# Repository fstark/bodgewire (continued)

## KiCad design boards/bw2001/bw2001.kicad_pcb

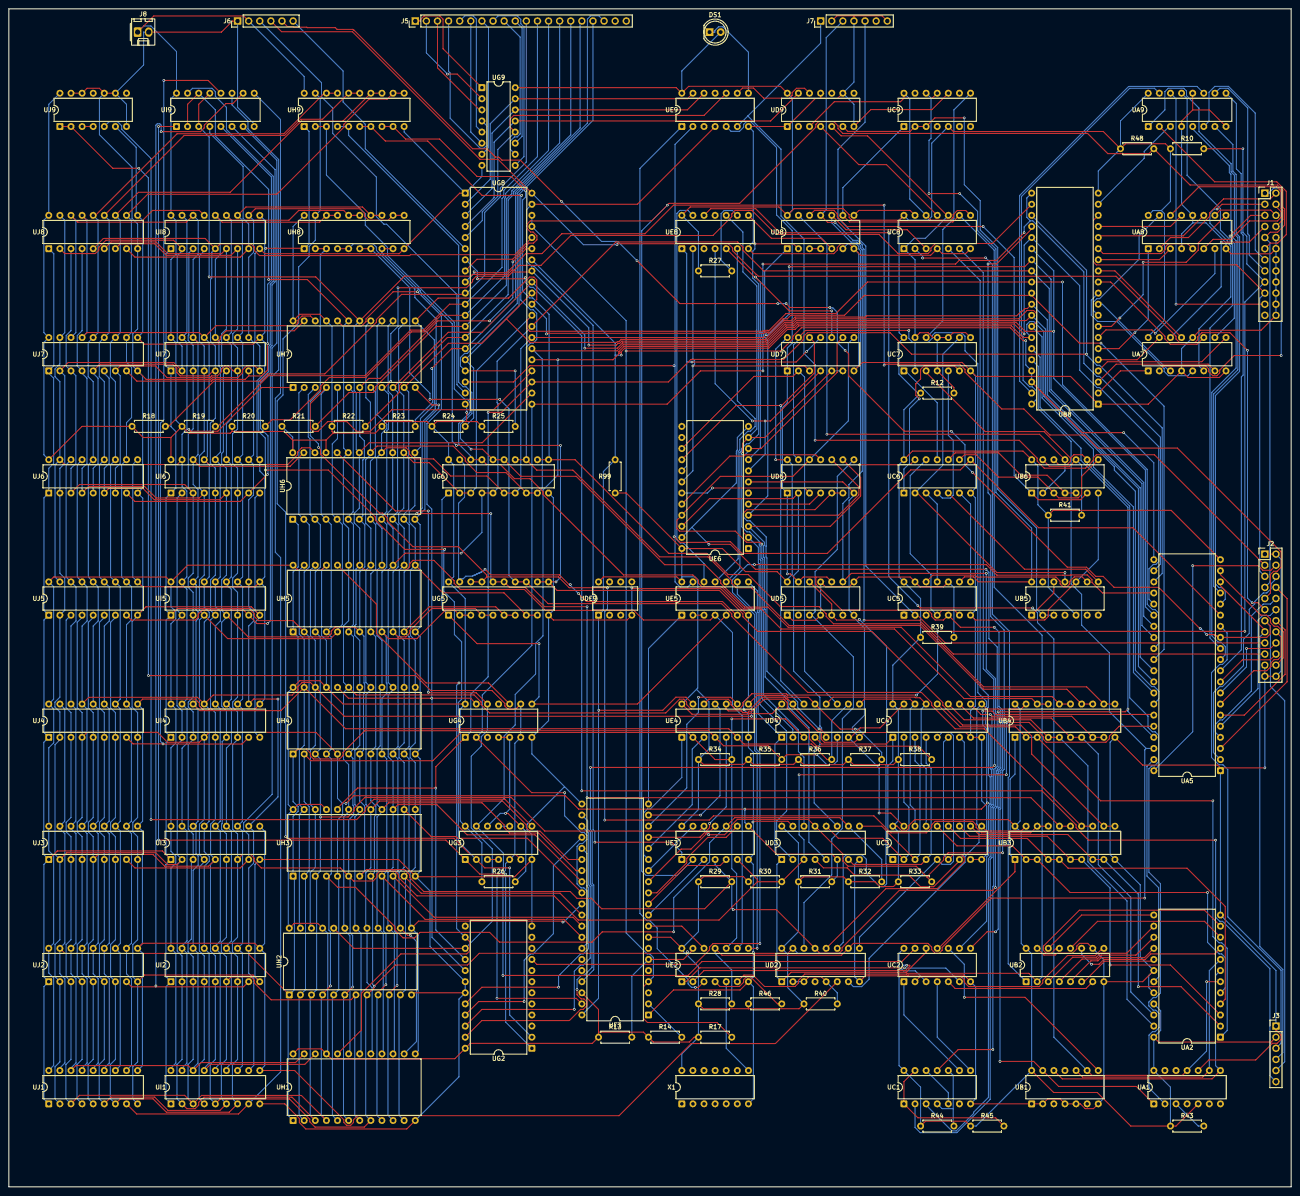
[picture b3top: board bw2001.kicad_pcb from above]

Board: 2 copper layers, 293.3 x 269.4 mm, 117 parts (0 on the bottom side), 278 nets.

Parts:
DS1: LED; LED_D5.0mm
J1: IEEE488; PinHeader_2x12_P2.54mm_Vertical
J2: USERPORT; PinHeader_2x12_P2.54mm_Vertical
J3, J6: CASSETTE; PinHeader_1x06_P2.54mm_Vertical
J5: MATRIXKB; PinHeader_1x20_P2.54mm_Vertical
J7: MONITOR; PinHeader_1x07_P2.54mm_Vertical
J8: POWER; Molex_KK-254_AE-6410-02A_1x02_P2.54mm_Vertical
R10, R48: 2k4; R_Axial_DIN0207_L6.3mm_D2.5mm_P7.62mm_Horizontal
R12, R13, R14, R26, R27, R28, R29, R30, R31, R32, R33, R34, R35, R36, R37, R38, R39, R40, R41, R43, R44, R45, R46: 1k; R_Axial_DIN0207_L6.3mm_D2.5mm_P7.62mm_Horizontal
R17, R99: 3k3; R_Axial_DIN0207_L6.3mm_D2.5mm_P7.62mm_Horizontal
R18, R19, R20, R21, R22, R23, R24, R25: 10k; R_Axial_DIN0207_L6.3mm_D2.5mm_P7.62mm_Horizontal
UA1: 74LS93; DIP-14_W7.62mm
UA2: 2316B; DIP-24_W15.24mm
UA5: 6522; DIP-40_W15.24mm
UA7, UA8, UA9: MC3446; DIP-16_W7.62mm
UB1: 74LS20; DIP-14_W7.62mm
UB2: 74LS165; DIP-16_W7.62mm
UB3, UB4: 74LS244; DIP-20_W7.62mm
UB5: 74LS93; DIP-14_W7.62mm
UB6: 74LS107; DIP-14_W7.62mm
UB8: 6520; DIP-40_W15.24mm
UC1: 74LS74; DIP-14_W7.62mm
UC2: 74LS00; DIP-14_W7.62mm
UC3, UC4: 2114; DIP-18_W7.62mm
UC5, UC7, UC8: 74LS107; DIP-14_W7.62mm
UC6: 74LS08; DIP-14_W7.62mm
UC9: 74LS93; DIP-14_W7.62mm
UD2, UD3, UD4: 74LS157; DIP-16_W7.62mm
UD5: 74LS107; DIP-14_W7.62mm
UD6, UD7: 74177; DIP-14_W7.62mm
UD8: 74LS00; DIP-14_W7.62mm
UD9: 74LS04; DIP-14_W7.62mm
UDE9: POR; DIP-8_W7.62mm
UE2: 74LS08; DIP-14_W7.62mm
UE3, UE4: 7417; DIP-14_W7.62mm
UE5: 74LS04; DIP-14_W7.62mm
UE6: 74100; DIP-24_W15.24mm
UE8, UE9: 74LS20; DIP-14_W7.62mm
UF3: 6502; DIP-40_W15.24mm
UG2: 74LS154; DIP-24_W15.24mm
UG3: 74LS00; DIP-14_W7.62mm
UG4: 74LS21; DIP-14_W7.62mm
UG5, UG6: 74LS244; DIP-20_W7.62mm
UG8: 6520; DIP-40_W15.24mm
UG9: 74LS145; DIP-16_W7.62mm
UH1, UH2, UH3, UH4, UH5, UH6, UH7: 2316B; DIP-24_W15.24mm
UH8, UH9: 74LS244; DIP-20_W7.62mm
UI1, UI2, UI3, UI4, UI5, UI6, UI7, UI8: 2114; DIP-18_W7.62mm
UI9: 74LS139; DIP-16_W7.62mm
UJ1, UJ2, UJ3, UJ4, UJ5, UJ6, UJ7, UJ8: 2114; DIP-18_W7.62mm
UJ9: 74LS00; DIP-14_W7.62mm
X1: OSC; DIP-14_W7.62mm

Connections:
A0: UE2.12 (4A), UF3.9 (A0)
A1: UE3.3 (2A), UF3.10 (A1)
A2: UE3.5 (3A), UF3.11 (A2)
A3: UE3.9 (4A), UF3.12 (A3)
A4: UE3.11 (5A), UF3.13 (A4)
A5: UE3.13 (6A), UF3.14 (A5)
A6: UE4.1 (1A), UF3.15 (A6)
A7: UE4.3 (2A), UF3.16 (A7)
A8: UE4.5 (3A), UF3.17 (A8)
A9: UE4.9 (4A), UF3.18 (A9)
A10: UE4.11 (5A), UF3.19 (A10)
A11: UE5.1 (1A), UF3.20 (A11)
A12: UF3.22 (A12), UG2.23 (A)
A13: UF3.23 (A13), UG2.22 (B)
A14: UF3.24 (A14), UG2.21 (C)
A15: UF3.25 (A15), UG2.20 (D)
ATN_IN_N: UA9.15 (RD), UB8.40 (CA1)
ATN_N: J1.21 (ATN_N), UA9.14 (BUSD)
ATN_OUT_N: UA5.12 (PB2), UA9.13 (DD)
BA0: R28.2, UA5.38 (RS0), UB8.36 (RS0), UD2.10 (3B), UE2.11 (4Y), UG8.36 (RS0), UH1.8 (A0), UH2.8 (A0), UH3.8 (A0), UH4.8 (A0), UH5.8 (A0), UH6.8 (A0), UH7.8 (A0), UI1.5 (A0), UI2.5 (A0), UI3.5 (A0), UI4.5 (A0), UI5.5 (A0), UI6.5 (A0), UI7.5 (A0), UI8.5 (A0), UJ1.5 (A0), UJ2.5 (A0), UJ3.5 (A0), UJ4.5 (A0), UJ5.5 (A0), UJ6.5 (A0), UJ7.5 (A0), UJ8.5 (A0)
BA1: R29.2, UA5.37 (RS1), UB8.35 (RS1), UD2.13 (4B), UE3.4 (2Y), UG8.35 (RS1), UH1.7 (A1), UH2.7 (A1), UH3.7 (A1), UH4.7 (A1), UH5.7 (A1), UH6.7 (A1), UH7.7 (A1), UI1.6 (A1), UI2.6 (A1), UI3.6 (A1), UI4.6 (A1), UI5.6 (A1), UI6.6 (A1), UI7.6 (A1), UI8.6 (A1), UJ1.6 (A1), UJ2.6 (A1), UJ3.6 (A1), UJ4.6 (A1), UJ5.6 (A1), UJ6.6 (A1), UJ7.6 (A1), UJ8.6 (A1)
BA2: R30.2, UA5.36 (RS2), UD3.3 (1B), UE3.6 (3Y), UH1.6 (A2), UH2.6 (A2), UH3.6 (A2), UH4.6 (A2), UH5.6 (A2), UH6.6 (A2), UH7.6 (A2), UI1.7 (A2), UI2.7 (A2), UI3.7 (A2), UI4.7 (A2), UI5.7 (A2), UI6.7 (A2), UI7.7 (A2), UI8.7 (A2), UJ1.7 (A2), UJ2.7 (A2), UJ3.7 (A2), UJ4.7 (A2), UJ5.7 (A2), UJ6.7 (A2), UJ7.7 (A2), UJ8.7 (A2)
BA3: R31.2, UA5.35 (RS3), UD3.6 (2B), UE3.8 (4Y), UH1.5 (A3), UH2.5 (A3), UH3.5 (A3), UH4.5 (A3), UH5.5 (A3), UH6.5 (A3), UH7.5 (A3), UI1.4 (A3), UI2.4 (A3), UI3.4 (A3), UI4.4 (A3), UI5.4 (A3), UI6.4 (A3), UI7.4 (A3), UI8.4 (A3), UJ1.4 (A3), UJ2.4 (A3), UJ3.4 (A3), UJ4.4 (A3), UJ5.4 (A3), UJ6.4 (A3), UJ7.4 (A3), UJ8.4 (A3)
BA4: R32.2, UD3.10 (3B), UE3.10 (5Y), UG8.24 (CS1), UH1.4 (A4), UH2.4 (A4), UH3.4 (A4), UH4.4 (A4), UH5.4 (A4), UH6.4 (A4), UH7.4 (A4), UI1.3 (A4), UI2.3 (A4), UI3.3 (A4), UI4.3 (A4), UI5.3 (A4), UI6.3 (A4), UI7.3 (A4), UI8.3 (A4), UJ1.3 (A4), UJ2.3 (A4), UJ3.3 (A4), UJ4.3 (A4), UJ5.3 (A4), UJ6.3 (A4), UJ7.3 (A4), UJ8.3 (A4)
BA5: R33.2, UB8.24 (CS1), UD3.13 (4B), UE3.12 (6Y), UH1.3 (A5), UH2.3 (A5), UH3.3 (A5), UH4.3 (A5), UH5.3 (A5), UH6.3 (A5), UH7.3 (A5), UI1.2 (A5), UI2.2 (A5), UI3.2 (A5), UI4.2 (A5), UI5.2 (A5), UI6.2 (A5), UI7.2 (A5), UI8.2 (A5), UJ1.2 (A5), UJ2.2 (A5), UJ3.2 (A5), UJ4.2 (A5), UJ5.2 (A5), UJ6.2 (A5), UJ7.2 (A5), UJ8.2 (A5)
BA6: R34.2, UD4.3 (1B), UE2.10 (3B), UE4.2 (1Y), UH1.2 (A6), UH2.2 (A6), UH3.2 (A6), UH4.2 (A6), UH5.2 (A6), UH6.2 (A6), UH7.2 (A6), UI1.1 (A6), UI2.1 (A6), UI3.1 (A6), UI4.1 (A6), UI5.1 (A6), UI6.1 (A6), UI7.1 (A6), UI8.1 (A6), UJ1.1 (A6), UJ2.1 (A6), UJ3.1 (A6), UJ4.1 (A6), UJ5.1 (A6), UJ6.1 (A6), UJ7.1 (A6), UJ8.1 (A6)
BA7: R35.2, UD4.6 (2B), UE4.4 (2Y), UH1.1 (A7), UH2.1 (A7), UH3.1 (A7), UH4.1 (A7), UH5.1 (A7), UH6.1 (A7), UH7.1 (A7), UI1.17 (A7), UI2.17 (A7), UI3.17 (A7), UI4.17 (A7), UI5.17 (A7), UI6.17 (A7), UI7.17 (A7), UI8.17 (A7), UJ1.17 (A7), UJ2.17 (A7), UJ3.17 (A7), UJ4.17 (A7), UJ5.17 (A7), UJ6.17 (A7), UJ7.17 (A7), UJ8.17 (A7)
BA8: R36.2, UD4.10 (3B), UE4.6 (3Y), UH1.23 (A8), UH2.23 (A8), UH3.23 (A8), UH4.23 (A8), UH5.23 (A8), UH6.23 (A8), UH7.23 (A8), UI1.16 (A8), UI2.16 (A8), UI3.16 (A8), UI4.16 (A8), UI5.16 (A8), UI6.16 (A8), UI7.16 (A8), UI8.16 (A8), UJ1.16 (A8), UJ2.16 (A8), UJ3.16 (A8), UJ4.16 (A8), UJ5.16 (A8), UJ6.16 (A8), UJ7.16 (A8), UJ8.16 (A8)
BA9: R37.2, UD4.13 (4B), UE4.8 (4Y), UH1.22 (A9), UH2.22 (A9), UH3.22 (A9), UH4.22 (A9), UH5.22 (A9), UH6.22 (A9), UH7.22 (A9), UI1.15 (A9), UI2.15 (A9), UI3.15 (A9), UI4.15 (A9), UI5.15 (A9), UI6.15 (A9), UI7.15 (A9), UI8.15 (A9), UJ1.15 (A9), UJ2.15 (A9), UJ3.15 (A9), UJ4.15 (A9), UJ5.15 (A9), UJ6.15 (A9), UJ7.15 (A9), UJ8.15 (A9)
BA10: R38.2, UE4.10 (5Y), UH1.19 (A10), UH2.19 (A10), UH3.19 (A10), UH4.19 (A10), UH5.19 (A10), UH6.19 (A10), UH7.19 (A10), UI9.2 (1A), UI9.14 (2A)
BA11: UB8.22 (CS0), UE2.9 (3A), UE5.4 (2Y), UG8.22 (CS0), UH1.18 (CS2), UH2.18 (CS2), UH3.18 (CS2), UH4.18 (CS2), UH5.18 (CS2), UH6.18 (CS2), UH7.18 (CS2), UI9.3 (1B), UI9.13 (2B)
BA11_N: UE5.2 (1Y), UE5.3 (2A)
BBD0: UH8.17 (2A4), UH8.18 (1Y1), UI1.14 (IO1), UI2.14 (IO1), UI3.14 (IO1), UI4.14 (IO1), UI5.14 (IO1), UI6.14 (IO1), UI7.14 (IO1), UI8.14 (IO1)
BBD1: UH8.15 (2A3), UH8.16 (1Y2), UI1.13 (IO2), UI2.13 (IO2), UI3.13 (IO2), UI4.13 (IO2), UI5.13 (IO2), UI6.13 (IO2), UI7.13 (IO2), UI8.13 (IO2)
BBD2: UH8.13 (2A2), UH8.14 (1Y3), UI1.12 (IO3), UI2.12 (IO3), UI3.12 (IO3), UI4.12 (IO3), UI5.12 (IO3), UI6.12 (IO3), UI7.12 (IO3), UI8.12 (IO3)
BBD3: UH8.11 (2A1), UH8.12 (1Y4), UI1.11 (IO4), UI2.11 (IO4), UI3.11 (IO4), UI4.11 (IO4), UI5.11 (IO4), UI6.11 (IO4), UI7.11 (IO4), UI8.11 (IO4)
BBD4: UH9.17 (2A4), UH9.18 (1Y1), UJ1.14 (IO1), UJ2.14 (IO1), UJ3.14 (IO1), UJ4.14 (IO1), UJ5.14 (IO1), UJ6.14 (IO1), UJ7.14 (IO1), UJ8.14 (IO1)
BBD5: UH9.15 (2A3), UH9.16 (1Y2), UJ1.13 (IO2), UJ2.13 (IO2), UJ3.13 (IO2), UJ4.13 (IO2), UJ5.13 (IO2), UJ6.13 (IO2), UJ7.13 (IO2), UJ8.13 (IO2)
BBD6: UH9.13 (2A2), UH9.14 (1Y3), UJ1.12 (IO3), UJ2.12 (IO3), UJ3.12 (IO3), UJ4.12 (IO3), UJ5.12 (IO3), UJ6.12 (IO3), UJ7.12 (IO3), UJ8.12 (IO3)
BBD7: UH9.11 (2A1), UH9.12 (1Y4), UJ1.11 (IO4), UJ2.11 (IO4), UJ3.11 (IO4), UJ4.11 (IO4), UJ5.11 (IO4), UJ6.11 (IO4), UJ7.11 (IO4), UJ8.11 (IO4)
BD0: UB3.17 (2A4), UB3.18 (1Y1), UG5.17 (2A4), UG5.18 (1Y1), UH8.2 (1A1), UH8.3 (2Y4)
BD1: UB3.15 (2A3), UB3.16 (1Y2), UG5.15 (2A3), UG5.16 (1Y2), UH8.4 (1A2), UH8.5 (2Y3)
BD2: UB3.13 (2A2), UB3.14 (1Y3), UG5.13 (2A2), UG5.14 (1Y3), UH8.6 (1A3), UH8.7 (2Y2)
BD3: UB3.11 (2A1), UB3.12 (1Y4), UG5.11 (2A1), UG5.12 (1Y4), UH8.8 (1A4), UH8.9 (2Y1)
BD4: UB4.17 (2A4), UB4.18 (1Y1), UG6.17 (2A4), UG6.18 (1Y1), UH9.2 (1A1), UH9.3 (2Y4)
BD5: UB4.15 (2A3), UB4.16 (1Y2), UG6.15 (2A3), UG6.16 (1Y2), UH9.4 (1A2), UH9.5 (2Y3)
BD6: UB4.13 (2A2), UB4.14 (1Y3), UG6.13 (2A2), UG6.14 (1Y3), UH9.6 (1A3), UH9.7 (2Y2)
BD7: UB4.11 (2A1), UB4.12 (1Y4), UG6.11 (2A1), UG6.12 (1Y4), UH9.8 (1A4), UH9.9 (2Y1)
BD_TO_D: UE5.5 (3A), UG4.8 (2Y), UG5.1 (1OE_N), UG6.1 (1OE_N)
BD_TO_D_N: UE5.6 (3Y), UG5.19 (2OE_N), UG6.19 (2OE_N)
BLANK_TV: UE3.1 (1A), UE9.4 (1C), UG8.39 (CA2)
BLKEND_N: UD8.5 (2B), UE8.8 (2Y)
BPHI2: UG3.8 (3Y), UJ9.5 (2B)
CASS1_MOTOR: J6.3 (MOTOR), UG8.19 (CB2)
CASS1_READ: J2.11 (READ1), J6.4 (READ), UG8.40 (CA1)
CASS1_SWITCH: J6.6 (SENSE), UG8.6 (PA4)
CASS2_MOTOR: J3.3 (MOTOR), UA5.14 (PB4)
CASS2_READ: J2.15 (READ2), J3.4 (READ), UA5.18 (CB1)
CASS2_SWITCH: J3.6 (SENSE), UG8.7 (PA5)
CASS_WRITE: J2.13 (WRITE), J3.5 (WRITE), J6.5 (WRITE), UA5.13 (PB3)
CD0: UA2.9 (O0), UB2.11 (A)
CD1: UA2.10 (O1), UB2.12 (B)
CD2: UA2.11 (O2), UB2.13 (C)
CD3: UA2.13 (O3), UB2.14 (D)
CD4: UA2.14 (O4), UB2.3 (E)
CD5: UA2.15 (O5), UB2.4 (F)
CD6: UA2.16 (O6), UB2.5 (G)
CD7: UA2.17 (O7), UB2.6 (H)
CHLOAD: UC1.11 (2CLK), UC8.3 (1Q), UD5.9 (2CLK), UD8.10 (3B)
CHLOAD_CLR_N: UC8.13 (1CLR_N), UD8.8 (3Y)
CHLOAD_N: UB2.1 (SH_LD_N), UC8.2 (1Q_N)
CLK1M: UC8.8 (2J), UC8.12 (1CLK), UC9.11 (QD), UC9.14 (CKA), UD9.3 (2A)
CLK1M_N: UC8.11 (2K), UD9.4 (2Y)
CLK2M: UC7.12 (1CLK), UC9.8 (QC)
CLK8: UB2.2 (CLK), UC8.9 (2CLK), UC9.1 (CKB), UD8.9 (3A), UE2.6 (2Y)
D0: UA5.33 (D0), UB8.33 (D0), UF3.33 (D0), UG5.2 (1A1), UG5.3 (2Y4), UG8.33 (D0), UH1.9 (O0), UH2.9 (O0), UH3.9 (O0), UH4.9 (O0), UH5.9 (O0), UH6.9 (O0), UH7.9 (O0)
D1: UA5.32 (D1), UB8.32 (D1), UF3.32 (D1), UG5.4 (1A2), UG5.5 (2Y3), UG8.32 (D1), UH1.10 (O1), UH2.10 (O1), UH3.10 (O1), UH4.10 (O1), UH5.10 (O1), UH6.10 (O1), UH7.10 (O1)
D2: UA5.31 (D2), UB8.31 (D2), UF3.31 (D2), UG5.6 (1A3), UG5.7 (2Y2), UG8.31 (D2), UH1.11 (O2), UH2.11 (O2), UH3.11 (O2), UH4.11 (O2), UH5.11 (O2), UH6.11 (O2), UH7.11 (O2)
D3: UA5.30 (D3), UB8.30 (D3), UF3.30 (D3), UG5.8 (1A4), UG5.9 (2Y1), UG8.30 (D3), UH1.13 (O3), UH2.13 (O3), UH3.13 (O3), UH4.13 (O3), UH5.13 (O3), UH6.13 (O3), UH7.13 (O3)
D4: UA5.29 (D4), UB8.29 (D4), UF3.29 (D4), UG6.2 (1A1), UG6.3 (2Y4), UG8.29 (D4), UH1.14 (O4), UH2.14 (O4), UH3.14 (O4), UH4.14 (O4), UH5.14 (O4), UH6.14 (O4), UH7.14 (O4)
D5: UA5.28 (D5), UB8.28 (D5), UF3.28 (D5), UG6.4 (1A2), UG6.5 (2Y3), UG8.28 (D5), UH1.15 (O5), UH2.15 (O5), UH3.15 (O5), UH4.15 (O5), UH5.15 (O5), UH6.15 (O5), UH7.15 (O5)
D6: UA5.27 (D6), UB8.27 (D6), UF3.27 (D6), UG6.6 (1A3), UG6.7 (2Y2), UG8.27 (D6), UH1.16 (O6), UH2.16 (O6), UH3.16 (O6), UH4.16 (O6), UH5.16 (O6), UH6.16 (O6), UH7.16 (O6)
D7: UA5.26 (D7), UB8.26 (D7), UF3.26 (D7), UG6.8 (1A4), UG6.9 (2Y1), UG8.26 (D7), UH1.17 (O7), UH2.17 (O7), UH3.17 (O7), UH4.17 (O7), UH5.17 (O7), UH6.17 (O7), UH7.17 (O7)
DAV_IN_N: UA5.17 (PB7), UA9.1 (RA)
DAV_N: J1.11 (DAV_N), UA9.2 (BUSA)
DAV_OUT_N: UA9.3 (DA), UB8.19 (CB2)
DI1: UA7.1 (RA), UB8.2 (PA0)
DI2: UA7.7 (RB), UB8.3 (PA1)
DI3: UA7.9 (RC), UB8.4 (PA2)
DI4: UA7.15 (RD), UB8.5 (PA3)
DI5: UA8.1 (RA), UB8.6 (PA4)
DI6: UA8.7 (RB), UB8.7 (PA5)
DI7: UA8.9 (RC), UB8.8 (PA6)
DI8: UA8.15 (RD), UB8.9 (PA7)
DIAG: J2.9 (DIAG), UG8.9 (PA7)
DIAG_LED_N: DS1.1 (K), UE9.8 (2Y)
DIO1: J1.1 (DIO1), UA7.2 (BUSA)
DIO2: J1.3 (DIO2), UA7.6 (BUSB)
DIO3: J1.5 (DIO3), UA7.10 (BUSC)
DIO4: J1.7 (DIO4), UA7.14 (BUSD)
DIO5: J1.2 (DIO5), UA8.2 (BUSA)
DIO6: J1.4 (DIO6), UA8.6 (BUSB)
DIO7: J1.6 (DIO7), UA8.10 (BUSC)
DIO8: J1.8 (DIO8), UA8.14 (BUSD)
DISON_CLR: UC5.11 (2K), UC6.3 (1Y)
DISON_SET: UC5.8 (2J), UC6.6 (2Y)
DIS_OFF: UC5.4 (1K), UC5.6 (2Q_N), UC6.12 (4A)
DIS_ON: UA1.1 (CKB), UB1.13 (2D), UC5.1 (1J), UC5.5 (2Q), UD5.10 (2CLR_N), UD5.13 (1CLR_N), UD6.1 (CT_LOAD_N), UD7.1 (CT_LOAD_N), UE9.5 (1D)
DO1: UA7.3 (DA), UB8.10 (PB0)
DO2: UA7.5 (DB), UB8.11 (PB1)
DO3: UA7.11 (DC), UB8.12 (PB2)
DO4: UA7.13 (DD), UB8.13 (PB3)
DO5: UA8.3 (DA), UB8.14 (PB4)
DO6: UA8.5 (DB), UB8.15 (PB5)
DO7: UA8.11 (DC), UB8.16 (PB6)
DO8: UA8.13 (DD), UB8.17 (PB7)
DOT: UB2.9 (QH), UC2.2 (1B)
DOT_N: UB2.7 (QH_N), UC2.5 (2B)
END25_N: UD8.3 (1Y), UD8.4 (2A)
EOI_N: J1.9 (EOI_N), J2.7 (EOI_N), R48.2, UE3.2 (1Y), UG8.8 (PA6)
G3_11: UG3.10 (3B), UG3.11 (4Y)
GND: J1.10 (REN), J1.12 (GND1), J1.14 (GND2), J1.16 (GND3), J1.18 (GND4), J1.20 (GND5), J1.22 (GND6), J1.24 (GND7), J2.1 (GND1), J2.2 (GND4), J2.21 (GND2), J2.23 (GND3), J2.24 (GND5), J3.1 (GND), J6.1 (GND), J7.2 (GND1), J7.4 (GND2), J7.7 (GND3), J8.2 (GND), UA1.10 (GND), UA2.12 (GND), UA2.18 (CS2), UA2.20 (CS1), UA5.1 (GND), UA7.4 (ENABC_N), UA7.8 (GND), UA7.12 (END_N), UA8.4 (ENABC_N), UA8.8 (GND), UA8.12 (END_N), UA9.4 (ENABC_N), UA9.8 (GND), UA9.12 (END_N), UB1.1 (1A), UB1.2 (1B), UB1.4 (1C), UB1.5 (1D), UB1.7 (GND), UB2.8 (GND), UB2.10 (SER), UB2.15 (CLK_INH), UB3.10 (GND), UB4.10 (GND), UB5.10 (GND), UB6.7 (GND), UB8.1 (GND), UC1.7 (GND), UC2.7 (GND), UC3.8 (CS_N), UC3.9 (GND), UC4.8 (CS_N), UC4.9 (GND), UC5.7 (GND), UC6.7 (GND), UC7.7 (GND), UC8.4 (1K), UC8.7 (GND), UC9.10 (GND), UD2.8 (GND), UD2.15 (G_N), UD3.8 (GND), UD3.15 (G_N), UD4.8 (GND), UD4.15 (G_N), UD5.7 (GND), UD6.7 (GND), UD7.7 (GND), UD8.7 (GND), UD9.1 (1A), UD9.7 (GND), UD9.9 (4A), UD9.11 (5A), UDE9.4 (GND), UE2.7 (GND), UE3.7 (GND), UE4.7 (GND), UE5.7 (GND), UE6.7 (GND), UE8.7 (GND), UE9.7 (GND), UF3.1 (GND), UF3.21 (GND2), UG2.12 (GND), UG2.18 (G1_N), UG2.19 (G2_N), UG3.7 (GND), UG4.7 (GND), UG5.10 (GND), UG6.10 (GND), UG8.1 (GND), UG9.8 (GND), UH1.12 (GND), UH2.12 (GND), UH3.12 (GND), UH4.12 (GND), UH5.12 (GND), UH6.12 (GND), UH7.12 (GND), UH8.10 (GND), UH9.10 (GND), UI1.9 (GND), UI2.9 (GND), UI3.9 (GND), UI4.9 (GND), UI5.9 (GND), UI6.9 (GND), UI7.9 (GND), UI8.9 (GND), UI9.8 (GND), UJ1.9 (GND), UJ2.9 (GND), UJ3.9 (GND), UJ4.9 (GND), UJ5.9 (GND), UJ6.9 (GND), UJ7.9 (GND), UJ8.9 (GND), UJ9.7 (GND), UJ9.9 (3A), UJ9.10 (3B), UJ9.12 (4A), UJ9.13 (4B), X1.7 (GND)
GRAPHIC: UA2.19 (A10), UA5.39 (CA2)
H0: UB5.14 (CKA), UC5.9 (2CLK), UC9.12 (QA)
H1: UB5.1 (CKB), UB5.12 (QA)
H2: UB5.9 (QB), UC5.12 (1CLK)
H3: UB5.8 (QC), UC6.5 (2B)
H4: UB5.11 (QD), UC6.2 (1B), UC7.9 (2CLK)
H5: UC6.4 (2A), UC7.5 (2Q)
H5_N: UC6.1 (1A), UC7.6 (2Q_N)
HCNT_CLR: UB5.2 (R01), UB5.3 (R02), UC9.2 (R01), UC9.3 (R02), UD9.6 (3Y)
HORZ_DRIVE: J2.17 (HORZ), J7.5 (HDRIVE), UC5.2 (1Q_N)
IFC_N: J1.17 (IFC_N), R10.2, UE4.12 (6Y)
IRQ_N: R17.2, UA5.21 (IRQ_N), UB8.37 (IRQB_N), UB8.38 (IRQA_N), UF3.4 (IRQ_N), UG8.37 (IRQB_N), UG8.38 (IRQA_N)
KEY_A: UE9.13 (2D), UG8.2 (PA0), UG9.15 (A)
KEY_B: UE9.12 (2C), UG8.3 (PA1), UG9.14 (B)
KEY_C: UD9.13 (6A), UG8.4 (PA2), UG9.13 (C)
KEY_C_N: UD9.12 (6Y), UE9.9 (2A)
KEY_D: UE9.10 (2B), UG8.5 (PA3), UG9.12 (D)
KIN0: J5.11 (COL0), R18.2, UG8.10 (PB0)
KIN1: J5.12 (COL1), R19.2, UG8.11 (PB1)
KIN2: J5.13 (COL2), R20.2, UG8.12 (PB2)
KIN3: J5.14 (COL3), R21.2, UG8.13 (PB3)
KIN4: J5.15 (COL4), R22.2, UG8.14 (PB4)
KIN5: J5.16 (COL5), R23.2, UG8.15 (PB5)
KIN6: J5.17 (COL6), R24.2, UG8.16 (PB6)
KIN7: J5.18 (COL7), R25.2, UG8.17 (PB7)
LA2: UD6.4 (A), UE6.5 (1Q1)
LA3: UD6.10 (B), UD8.1 (1A), UE6.4 (1Q2)
LA4: UD6.3 (C), UE6.19 (1Q3)
LA5: UD6.11 (D), UE6.20 (1Q4)
LA6: UD7.4 (A), UE6.8 (2Q1), UE8.4 (1C)
LA7: UD7.10 (B), UE6.9 (2Q2), UE8.5 (1D)
LA8: UD7.3 (C), UE6.18 (2Q3), UE8.2 (1B)
LA9: UD7.11 (D), UE6.17 (2Q4), UE8.1 (1A)
LATCH_G: UC2.8 (3Y), UE6.12 (2G), UE6.23 (1G)
LAT_HI: UD8.2 (1B), UE5.10 (5Y)
LAT_HI_N: UE5.11 (5A), UE8.6 (1Y)
NDAC_IN_N: UA5.10 (PB0), UA9.9 (RC)
NDAC_N: J1.15 (NDAC_N), UA9.10 (BUSC)
NDAC_OUT_N: UA9.11 (DC), UB8.39 (CA2)
NMI_N: R13.2, UE2.13 (4B), UF3.6 (NMI_N)
NRFD_IN_N: UA5.16 (PB6), UA9.7 (RB)
NRFD_N: J1.13 (NRFD_N), UA9.6 (BUSB)
NRFD_OUT_N: UA5.11 (PB1), UA9.5 (DB)
OSC8: UE2.5 (2B), X1.8 (OUT)
PA0: J2.6 (PA0), UA5.2 (PA0)
PA1: J2.8 (PA1), UA5.3 (PA1)
PA2: J2.10 (PA2), UA5.4 (PA2)
PA3: J2.12 (PA3), UA5.5 (PA3)
PA4: J2.14 (PA4), UA5.6 (PA4)
PA5: J2.16 (PA5), UA5.7 (PA5)
PA6: J2.18 (PA6), UA5.8 (PA6)
PA7: J2.20 (PA7), UA5.9 (PA7)
PHI0: UC8.6 (2Q_N), UF3.37 (PHI0)
PHI0_N: UC1.3 (1CLK), UC8.5 (2Q)
PHI2: UA5.25 (PHI2), UB8.25 (PHI2), UF3.39 (PHI2), UG3.13 (4B), UG8.25 (PHI2)
PIXEL: UE2.3 (1Y), UE9.1 (1A)
PIX_A_N: UC2.3 (1Y), UE2.2 (1B)
PIX_B_N: UC2.6 (2Y), UE2.1 (1A)
PU_R12: R12.2, UC7.4 (1K), UC7.8 (2J), UC7.10 (2CLR_N), UC7.11 (2K), UC7.13 (1CLR_N), UC8.1 (1J), UC8.10 (2CLR_N), UD9.5 (3A)
PU_R26: R26.2, UG3.9 (3A), UG3.12 (4A), UG4.4 (1C), UG4.5 (1D)
PU_R27: R27.2, UE8.9 (2A)
PU_R39: R39.2, UC5.10 (2CLR_N), UC5.13 (1CLR_N), UD5.1 (1J), UD5.4 (1K), UD5.8 (2J), UD5.11 (2K)
PU_R40: R40.2, UD2.2 (1A), UD2.3 (1B), UD2.5 (2A)
PU_R41: R41.2, UB6.10 (2CLR_N), UB6.13 (1CLR_N)
PU_R43: R43.2, UA1.3 (R02)
PU_R44: R44.2, UC1.4 (1PRE_N), UC1.10 (2PRE_N)
PU_R45: R45.2, UC1.1 (1CLR_N), UC1.13 (2CLR_N)
PU_R46: R46.2, UE2.4 (2A)
RA0: UA1.9 (QB), UA2.8 (A0), UB1.10 (2B)
RA1: UA1.8 (QC), UA2.7 (A1), UB1.12 (2C)
RA2: UA1.11 (QD), UA2.6 (A2), UB1.9 (2A), UE8.12 (2C)
RAM0_N: UI8.8 (CS_N), UI9.4 (1Y0_N), UJ8.8 (CS_N)
RAM1_N: UI7.8 (CS_N), UI9.5 (1Y1_N), UJ7.8 (CS_N)
RAM2_N: UI6.8 (CS_N), UI9.6 (1Y2_N), UJ6.8 (CS_N)
RAM3_N: UI5.8 (CS_N), UI9.7 (1Y3_N), UJ5.8 (CS_N)
RAM4_N: UI4.8 (CS_N), UI9.12 (2Y0_N), UJ4.8 (CS_N)
RAM5_N: UI3.8 (CS_N), UI9.11 (2Y1_N), UJ3.8 (CS_N)
RAM6_N: UI2.8 (CS_N), UI9.10 (2Y2_N), UJ2.8 (CS_N)
RAM7_N: UI1.8 (CS_N), UI9.9 (2Y3_N), UJ1.8 (CS_N)
RAMSEL: UG3.3 (1Y), UG3.4 (2A)
RAM_READ_N: UG3.6 (2Y), UH8.19 (2OE_N), UH9.19 (2OE_N)
RDY: R14.2, UF3.2 (RDY)
RES_N: R99.2, UA5.34 (RES_N), UB8.34 (RES_N), UDE9.1 (RST_N), UE4.13 (6A), UF3.40 (RES_N), UG8.34 (RES_N)
REV: UC1.9 (2Q), UC2.1 (1A)
REV_D: UC1.5 (1Q), UC1.12 (2D)
REV_N: UC1.8 (2Q_N), UC2.4 (2A)
ROW0: J5.1 (ROW0), UG9.1 (Y0_N)
ROW1: J5.2 (ROW1), UG9.2 (Y1_N)
ROW2: J5.3 (ROW2), UG9.3 (Y2_N)
ROW3: J5.4 (ROW3), UG9.4 (Y3_N)
ROW4: J5.5 (ROW4), UG9.5 (Y4_N)
ROW5: J5.6 (ROW5), UG9.6 (Y5_N)
ROW6: J5.7 (ROW6), UG9.7 (Y6_N)
ROW7: J5.8 (ROW7), UG9.9 (Y7_N)
ROW7_N: UB1.8 (2Y), UC2.10 (3B)
ROW8: J5.9 (ROW8), UG9.10 (Y8_N)
ROW9: J5.10 (ROW9), UG9.11 (Y9_N)
RW: UA5.22 (RW), UB8.21 (RW), UF3.34 (RW), UG4.2 (1B), UG8.21 (RW)
RW_E: UC2.13 (4B), UG3.5 (2B), UG4.6 (1Y), UG4.9 (2A), UJ9.1 (1A), UJ9.2 (1B)
RW_E_INV: UJ9.3 (1Y), UJ9.4 (2A)
RW_RAM: UD2.6 (2B), UH8.1 (1OE_N), UH9.1 (1OE_N), UI1.10 (WE_N), UI2.10 (WE_N), UI3.10 (WE_N), UI4.10 (WE_N), UI5.10 (WE_N), UI6.10 (WE_N), UI7.10 (WE_N), UI8.10 (WE_N), UJ1.10 (WE_N), UJ2.10 (WE_N), UJ3.10 (WE_N), UJ4.10 (WE_N), UJ5.10 (WE_N), UJ6.10 (WE_N), UJ7.10 (WE_N), UJ8.10 (WE_N), UJ9.6 (2Y)
SA0: UC3.5 (A0), UC4.5 (A0), UD2.9 (3Y)
SA1: UC3.6 (A1), UC4.6 (A1), UD2.12 (4Y)
SA2: UC3.7 (A2), UC4.7 (A2), UD3.4 (1Y)
SA3: UC3.4 (A3), UC4.4 (A3), UD3.7 (2Y)
SA4: UC3.3 (A4), UC4.3 (A4), UD3.9 (3Y)
SA5: UC3.2 (A5), UC4.2 (A5), UD3.12 (4Y)
SA6: UC3.1 (A6), UC4.1 (A6), UD4.4 (1Y)
SA7: UC3.17 (A7), UC4.17 (A7), UD4.7 (2Y)
SA8: UC3.16 (A8), UC4.16 (A8), UD4.9 (3Y)
SA9: UC3.15 (A9), UC4.15 (A9), UD4.12 (4Y)
SD0: UA2.5 (A3), UB3.2 (1A1), UB3.3 (2Y4), UC3.14 (IO1)
SD1: UA2.4 (A4), UB3.4 (1A2), UB3.5 (2Y3), UC3.13 (IO2)
SD2: UA2.3 (A5), UB3.6 (1A3), UB3.7 (2Y2), UC3.12 (IO3)
SD3: UA2.2 (A6), UB3.8 (1A4), UB3.9 (2Y1), UC3.11 (IO4)
SD4: UA2.1 (A7), UB4.2 (1A1), UB4.3 (2Y4), UC4.14 (IO1)
SD5: UA2.23 (A8), UB4.4 (1A2), UB4.5 (2Y3), UC4.13 (IO2)
SD6: UA2.22 (A9), UB4.6 (1A3), UB4.7 (2Y2), UC4.12 (IO3)
SD7: UB4.8 (1A4), UB4.9 (2Y1), UC1.2 (1D), UC4.11 (IO4)
SEL0_N: UG2.1 (Y0_N), UG3.1 (1A), UI9.1 (1G_N)
SEL1_N: UG2.2 (Y1_N), UG3.2 (1B), UI9.15 (2G_N)
SEL8: UC2.12 (4A), UD2.1 (S), UD3.1 (S), UD4.1 (S), UE5.8 (4Y)
SEL8_N: UE5.9 (4A), UG2.9 (Y8_N)
SELC_N: UG2.14 (Y12_N), UG4.10 (2B), UH1.20 (CS1), UH5.20 (CS1)
SELD_N: UG2.15 (Y13_N), UG4.12 (2C), UH2.20 (CS1), UH6.20 (CS1)
SELE_N: UA5.23 (CS2_N), UB8.23 (CS2_N), UG2.16 (Y14_N), UG4.1 (1A), UG8.23 (CS2_N), UH3.20 (CS1)
SELF_N: UG2.17 (Y15_N), UG4.13 (2D), UH4.20 (CS1), UH7.20 (CS1)
SRQ_N: J1.19 (SRQ_N), J2.5 (SRQ_N), UB8.18 (CB1)
SYNC_N: UE5.12 (6Y), UE8.13 (2D)
TA0: UD2.11 (3A), UD5.5 (2Q), UD5.12 (1CLK)
TA1: UD2.14 (4A), UD5.3 (1Q), UD6.8 (CLK1)
TA2: UD3.2 (1A), UD6.5 (QA), UD6.6 (CLK2), UE6.2 (1D1)
TA3: UD3.5 (2A), UD6.9 (QB), UE6.3 (1D2)
TA4: UD3.11 (3A), UD6.2 (QC), UE6.22 (1D3)
TA5: UD3.14 (4A), UD6.12 (QD), UD7.8 (CLK1), UE6.21 (1D4)
TA6: UD4.2 (1A), UD7.5 (QA), UD7.6 (CLK2), UE6.11 (2D1), UE8.10 (2B)
TA7: UD4.5 (2A), UD7.9 (QB), UE6.10 (2D2)
TA8: UD4.11 (3A), UD7.2 (QC), UE6.15 (2D3)
TA9: UD4.14 (4A), UD7.12 (QD), UE6.16 (2D4)
TV_VIDEO: J2.3 (VIDEO), J7.1 (VIDEO_N), UE9.6 (1Y)
USR_CA1: J2.4 (CA1), UA5.40 (CA1)
USR_CB2: J2.22 (CB2), UA5.19 (CB2)
VCC: DS1.2 (A), J3.2 (VCC), J6.2 (VCC), J8.1 (VCC), R10.1, R12.1, R13.1, R14.1, R17.1, R18.1, R19.1, R20.1, R21.1, R22.1, R23.1, R24.1, R25.1, R26.1, R27.1, R28.1, R29.1, R30.1, R31.1, R32.1, R33.1, R34.1, R35.1, R36.1, R37.1, R38.1, R39.1, R40.1, R41.1, R43.1, R44.1, R45.1, R46.1, R48.1, R99.1, UA1.5 (VCC), UA1.14 (CKA), UA2.21 (CS3), UA2.24 (VCC), UA5.20 (VCC), UA7.16 (VCC), UA8.16 (VCC), UA9.16 (VCC), UB1.14 (VCC), UB2.16 (VCC), UB3.20 (VCC), UB4.20 (VCC), UB5.5 (VCC), UB6.14 (VCC), UB8.20 (VCC), UC1.14 (VCC), UC2.14 (VCC), UC3.18 (VCC), UC4.18 (VCC), UC5.14 (VCC), UC6.14 (VCC), UC7.14 (VCC), UC8.14 (VCC), UC9.5 (VCC), UD2.16 (VCC), UD3.16 (VCC), UD4.16 (VCC), UD5.14 (VCC), UD6.14 (VCC), UD7.14 (VCC), UD8.14 (VCC), UD9.14 (VCC), UDE9.8 (VCC), UE2.14 (VCC), UE3.14 (VCC), UE4.14 (VCC), UE5.14 (VCC), UE6.24 (VCC), UE8.14 (VCC), UE9.14 (VCC), UF3.8 (VCC), UF3.38 (SO), UG2.24 (VCC), UG3.14 (VCC), UG4.14 (VCC), UG5.20 (VCC), UG6.20 (VCC), UG8.20 (VCC), UG9.16 (VCC), UH1.21 (CS3), UH1.24 (VCC), UH2.21 (CS3), UH2.24 (VCC), UH3.21 (CS3), UH3.24 (VCC), UH4.21 (CS3), UH4.24 (VCC), UH5.21 (CS3), UH5.24 (VCC), UH6.21 (CS3), UH6.24 (VCC), UH7.21 (CS3), UH7.24 (VCC), UH8.20 (VCC), UH9.20 (VCC), UI1.18 (VCC), UI2.18 (VCC), UI3.18 (VCC), UI4.18 (VCC), UI5.18 (VCC), UI6.18 (VCC), UI7.18 (VCC), UI8.18 (VCC), UI9.16 (VCC), UJ1.18 (VCC), UJ2.18 (VCC), UJ3.18 (VCC), UJ4.18 (VCC), UJ5.18 (VCC), UJ6.18 (VCC), UJ7.18 (VCC), UJ8.18 (VCC), UJ9.14 (VCC), X1.14 (VCC)
VEND: UC6.13 (4B), UD8.6 (2Y)
VERT_DRIVE: J2.19 (VERT), J7.3 (VDRIVE), UD8.11 (4Y)
VIA_CS1: UA5.24 (CS1), UE2.8 (3Y)
VIDEO_ON: UA5.15 (PB5), UC6.8 (3Y), UE5.13 (6A), UE9.2 (1B), UG8.18 (CB1)
VREAD_N: UB3.1 (1OE_N), UB4.1 (1OE_N), UC2.11 (4Y)
VRW_N: UB3.19 (2OE_N), UB4.19 (2OE_N), UC3.10 (WE_N), UC4.10 (WE_N), UD2.7 (2Y)
VS0: UB6.3 (1Q), UB6.8 (2J), UC6.9 (3A)
VS0_N: UB6.2 (1Q_N), UB6.11 (2K), UD8.13 (4B)
VS1: UB6.4 (1K), UB6.5 (2Q), UC6.10 (3B)
VS1_N: UB6.1 (1J), UB6.6 (2Q_N), UD8.12 (4A)
VSTEP: UA1.2 (R01), UB6.9 (2CLK), UB6.12 (1CLK), UC7.3 (1Q)
VSTEP_J: UC6.11 (4Y), UC7.1 (1J)
VSTEP_N: UC2.9 (3A), UC7.2 (1Q_N), UD6.13 (CLR_N), UD7.13 (CLR_N)

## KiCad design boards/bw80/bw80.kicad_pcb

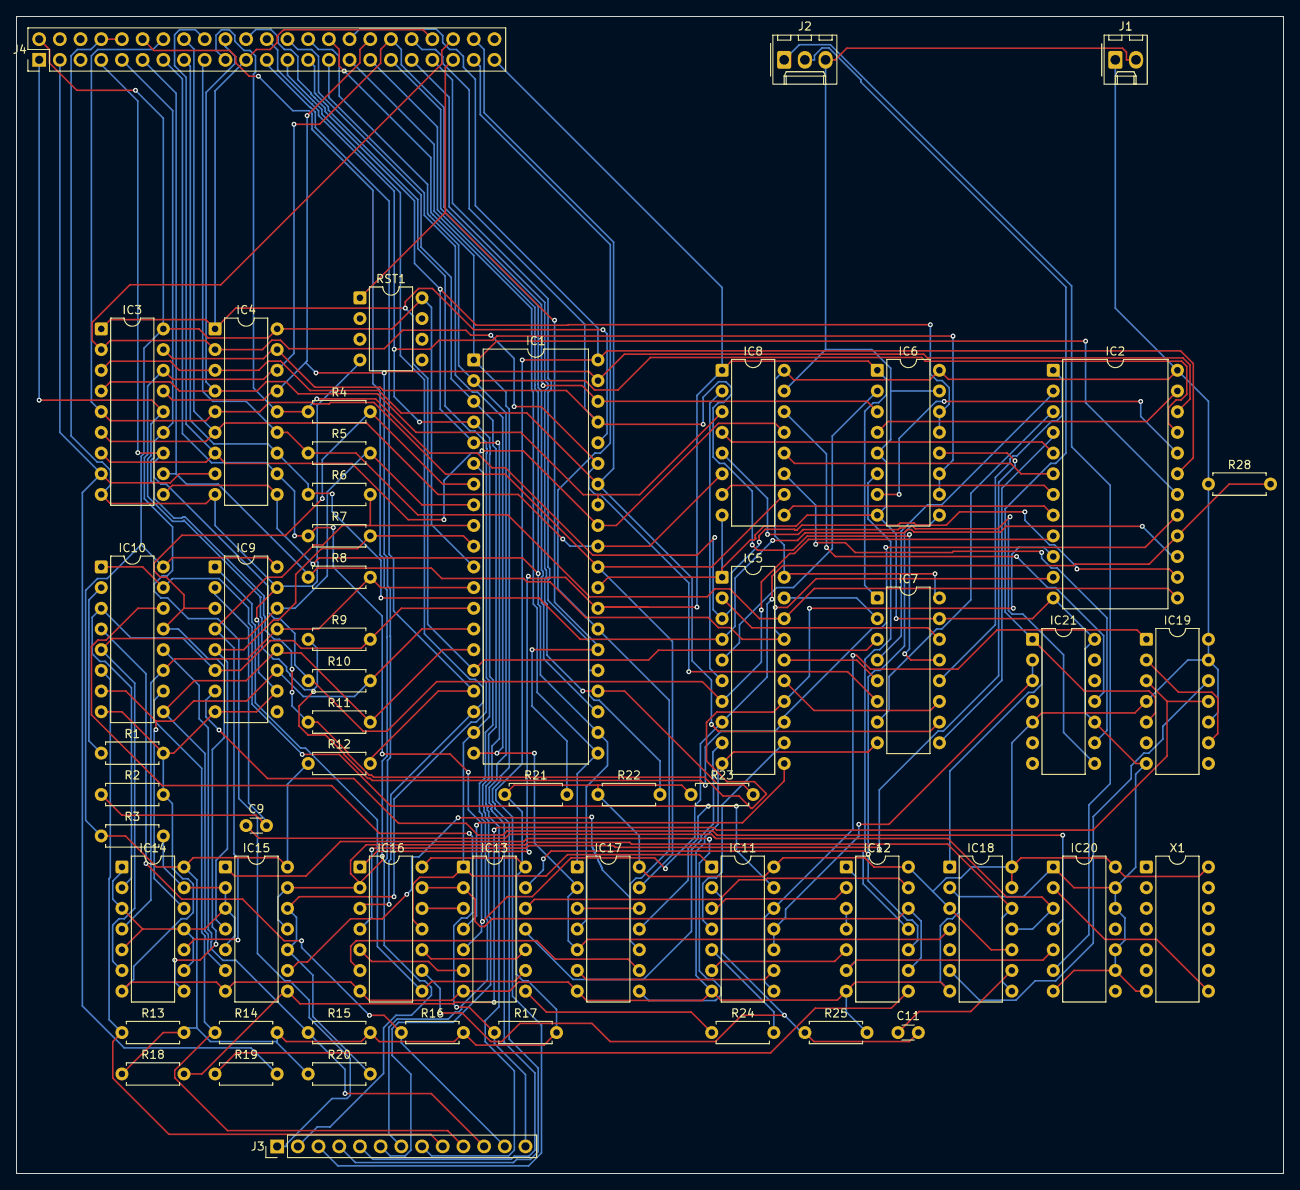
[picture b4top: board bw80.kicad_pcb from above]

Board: 2 copper layers, 155.5 x 142.0 mm, 55 parts (0 on the bottom side), 112 nets.

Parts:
C9, C11: 47p; C_Disc_D3.0mm_W1.6mm_P2.50mm
IC1: Z80; DIP-40_W15.24mm
IC2: 2332; DIP-24_W15.24mm
IC3, IC4: 2114; DIP-18_W7.62mm
IC5: 74LS373; DIP-20_W7.62mm
IC6, IC7, IC8: 74LS157; DIP-16_W7.62mm
IC9: 74LS165; DIP-16_W7.62mm
IC10: 74LS365; DIP-16_W7.62mm
IC11, IC12: 74LS00; DIP-14_W7.62mm
IC13: 74LS04; DIP-14_W7.62mm
IC14, IC15: 74LS05; DIP-14_W7.62mm
IC16: 74LS10; DIP-14_W7.62mm
IC17: 74LS32; DIP-14_W7.62mm
IC18, IC19: 74LS74; DIP-14_W7.62mm
IC20: 74LS86; DIP-14_W7.62mm
IC21: 74LS93; DIP-14_W7.62mm
J1: POWER; Molex_KK-254_AE-6410-02A_1x02_P2.54mm_Vertical
J2: VIDEO; Molex_KK-254_AE-6410-03A_1x03_P2.54mm_Vertical
J3: MEMBRANEKB; PinHeader_1x13_P2.54mm_Vertical
J4: EXPANSION; PinHeader_2x23_P2.54mm_Vertical
R1, R3, R4, R5, R6, R7, R8, R9, R10, R11, R12, R18, R22, R23, R24: 1k; R_Axial_DIN0207_L6.3mm_D2.5mm_P7.62mm_Horizontal
R2, R25: 470; R_Axial_DIN0207_L6.3mm_D2.5mm_P7.62mm_Horizontal
R13, R14, R15, R16, R17, R28: 47k; R_Axial_DIN0207_L6.3mm_D2.5mm_P7.62mm_Horizontal
R19: 2k2; R_Axial_DIN0207_L6.3mm_D2.5mm_P7.62mm_Horizontal
R20: 330; R_Axial_DIN0207_L6.3mm_D2.5mm_P7.62mm_Horizontal
R21: 220k; R_Axial_DIN0207_L6.3mm_D2.5mm_P7.62mm_Horizontal
RST1: POR; DIP-8_W7.62mm
X1: OSC; DIP-14_W7.62mm

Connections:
A0: IC1.30 (A0), IC3.5 (A0), IC4.5 (A0), IC8.10 (3B), IC17.13 (4B), J4.14 (A0)
A1: IC1.31 (A1), IC3.6 (A1), IC4.6 (A1), IC8.6 (2B), J4.16 (A1)
A2: IC1.32 (A2), IC3.7 (A2), IC4.7 (A2), IC8.13 (4B), J4.18 (A2)
A3: IC1.33 (A3), IC3.4 (A3), IC4.4 (A3), IC8.3 (1B), J4.20 (A3)
A4: IC1.34 (A4), IC3.3 (A4), IC4.3 (A4), IC7.10 (3B), J4.44 (A4)
A5: IC1.35 (A5), IC3.2 (A5), IC4.2 (A5), IC7.6 (2B), J4.42 (A5)
A6: IC1.16 (INT_N), IC1.36 (A6), IC3.1 (A6), IC4.1 (A6), IC7.3 (1B), J4.21 (INT_N), J4.40 (A6)
A7: IC1.37 (A7), IC3.17 (A7), IC4.17 (A7), IC7.13 (4B), J4.38 (A7)
A8: IC1.38 (A8), IC3.16 (A8), IC4.16 (A8), IC6.3 (1B), J3.1 (A8), J4.36 (A8)
A9: IC1.39 (A9), IC2.22 (A9), IC3.15 (A9), IC4.15 (A9), J3.2 (A9), J4.34 (A9)
A10: IC1.40 (A10), IC2.19 (A10), J3.3 (A10), J4.32 (A10)
A11: IC1.1 (A11), IC2.18 (A11), J3.4 (A11), J4.30 (A11)
A12: IC1.2 (A12), IC2.21 (CS2), J3.5 (A12), J4.28 (A12)
A13: IC1.3 (A13), J3.6 (A13), J4.26 (A13)
A14: IC1.4 (A14), IC6.10 (3B), IC6.11 (3A), J3.7 (A14), J4.24 (A14)
A14B: IC6.9 (3Y), IC12.10 (3B), IC13.13 (6A)
A14B_N: IC12.13 (4B), IC13.12 (6Y)
A15: IC1.5 (A15), IC6.13 (4B), IC6.14 (4A), J3.8 (A15), J4.22 (A15)
A15B: IC6.12 (4Y), IC16.4 (2B)
BUSAK_N: IC1.23 (BUSAK_N), J4.35 (BUSAK_N)
BUSRQ_N: IC1.25 (BUSRQ_N), J4.39 (BUSRQ_N), R22.2
CH0: IC5.6 (3Q), IC8.2 (1A)
CH1: IC5.15 (6Q), IC7.11 (3A)
CH2: IC5.16 (7Q), IC7.5 (2A)
CH3: IC5.19 (8Q), IC7.2 (1A)
CH4: IC5.2 (1Q), IC7.14 (4A)
CH5: IC5.5 (2Q), IC6.2 (1A)
CH6: IC5.9 (4Q), IC13.11 (5A)
CH6_N: IC13.10 (5Y), IC16.10 (3B)
CH7: IC5.12 (5Q), IC11.4 (2A)
CLK: IC1.6 (CLK), IC15.10 (5Y), IC15.12 (6Y), R20.2
D0: IC1.14 (D0), IC9.11 (A), IC10.7 (Y3), IC14.12 (6Y), R10.2
D1: IC1.15 (D1), IC9.12 (B), IC10.9 (Y4), IC15.6 (3Y), R11.2
D2: IC1.12 (D2), IC9.13 (C), IC10.11 (Y5), IC14.4 (2Y), R8.2
D3: IC1.8 (D3), IC9.14 (D), IC10.5 (Y2), IC14.6 (3Y), R5.2
D4: IC1.7 (D4), IC9.3 (E), IC10.13 (Y6), IC14.8 (4Y), R4.2
D5: IC1.9 (D5), IC9.4 (F), IC14.10 (5Y), R6.2
D6: IC1.10 (D6), IC9.5 (G), IC15.4 (2Y), R7.2
D7: IC1.13 (D7), IC9.6 (H), IC10.3 (Y1), IC14.2 (1Y), R9.2
DOT: IC20.2 (1B), X1.8 (OUT)
DOT2: C9.1, IC18.11 (2CLK), IC20.3 (1Y)
EAR: IC10.2 (A1), R1.1
GND: IC1.29 (GND), IC2.12 (GND), IC3.9 (GND), IC4.9 (GND), IC5.1 (OE_N), IC5.10 (GND), IC6.5 (2A), IC6.8 (GND), IC6.15 (G_N), IC7.8 (GND), IC7.15 (G_N), IC8.8 (GND), IC8.15 (G_N), IC9.8 (GND), IC9.10 (SER), IC9.15 (CLK_INH), IC10.8 (GND), IC11.7 (GND), IC12.7 (GND), IC13.7 (GND), IC14.7 (GND), IC15.7 (GND), IC16.7 (GND), IC17.7 (GND), IC18.2 (1D), IC18.7 (GND), IC19.7 (GND), IC20.1 (1A), IC20.7 (GND), IC20.9 (3A), IC20.10 (3B), IC20.12 (4A), IC20.13 (4B), IC21.10 (GND), IC21.14 (CKA), J1.2 (GND), J2.3 (GND), J4.8 (GND1), J4.10 (GND2), R1.2, R2.2, R25.2, RST1.4 (GND), X1.7 (GND)
HALT_N: IC1.18 (HALT_N), IC16.3 (2A), J4.25 (HALT_N)
INV: IC12.1 (1A), IC12.6 (2Y), IC20.5 (2B)
INV_N: IC12.3 (1Y), IC12.4 (2A)
INV_SET_N: IC11.6 (2Y), IC12.5 (2B)
INV_STROBE_N: IC11.3 (1Y), IC12.2 (1B)
IORD_N: IC17.3 (1Y), IC17.12 (4A)
IORQ_N: IC1.20 (IORQ_N), IC17.2 (1B), IC17.5 (2B), IC18.4 (1PRE_N), J4.29 (IORQ_N)
IOWR_N: IC11.9 (3A), IC17.6 (2Y)
KB0: IC10.6 (A3), J3.9 (KB0), R13.1
KB1: IC10.10 (A4), J3.10 (KB1), R14.1
KB2: IC10.12 (A5), J3.11 (KB2), R15.1
KB3: IC10.4 (A2), J3.12 (KB3), R16.1
KB4: IC10.14 (A6), J3.13 (KB4), R17.1
KBD_N: IC10.1 (G1_N), IC10.15 (G2_N), IC11.13 (4B), IC17.11 (4Y)
LC0: IC8.11 (3A), IC21.9 (QB)
LC1: IC8.5 (2A), IC21.8 (QC)
LC2: IC8.14 (4A), IC21.11 (QD)
LE: IC5.11 (LE), IC13.4 (2Y)
LE_N: IC13.3 (2A), IC16.12 (1Y)
LOAD: IC13.8 (4Y), R24.1
LOAD_N: IC9.1 (SH_LD_N), IC13.9 (4A), IC16.8 (3Y)
LOAD_PULSE: C11.2, IC11.2 (1B), IC16.9 (3A), R25.1
LOAD_R: IC11.5 (2B), R24.2
M1_CLK: IC15.8 (4Y), IC19.3 (1CLK), IC19.11 (2CLK), R18.2
M1_N: IC1.27 (M1_N), IC15.9 (4A), IC17.10 (3B), J4.43 (M1_N)
MD0: IC2.9 (O0), IC3.12 (IO3), IC5.7 (3D), J4.7 (D0), R10.1
MD1: IC2.10 (O1), IC3.13 (IO2), IC5.14 (6D), J4.9 (D1), R11.1
MD2: IC2.11 (O2), IC3.11 (IO4), IC5.17 (7D), J4.11 (D2), R8.1
MD3: IC2.13 (O3), IC4.13 (IO2), IC5.18 (8D), J4.17 (D3), R5.1
MD4: IC2.14 (O4), IC4.14 (IO1), IC5.3 (1D), J4.19 (D4), R4.1
MD5: IC2.15 (O5), IC4.12 (IO3), IC5.4 (2D), J4.15 (D5), R6.1
MD6: IC2.16 (O6), IC4.11 (IO4), IC5.8 (4D), IC13.5 (3A), J4.13 (D6), R7.1, R28.2
MD6_N: IC13.6 (3Y), IC16.5 (2C)
MD7: IC2.17 (O7), IC3.14 (IO1), IC5.13 (5D), J4.1 (D7), R9.1
MREQ: IC12.9 (3A), IC12.12 (4A), IC13.2 (1Y), IC16.13 (1C)
MREQ_N: IC1.19 (MREQ_N), IC11.1 (1A), IC13.1 (1A), IC16.11 (3C), J4.27 (MREQ_N)
NMI_N: IC1.17 (NMI_N), J4.23 (NMI_N), R12.2
NOP_COND_N: IC16.6 (2Y), IC17.9 (3A)
NOP_EN: IC14.1 (1A), IC14.3 (2A), IC14.5 (3A), IC14.9 (4A), IC14.11 (5A), IC14.13 (6A), IC15.2 (1Y), IC15.3 (2A), IC15.5 (3A), R3.2
NOP_N: IC15.1 (1A), IC17.8 (3Y)
PHI: C11.1, IC18.9 (2Q)
PHI_N: IC15.11 (5A), IC15.13 (6A), IC16.2 (1B), IC18.8 (2Q_N), IC18.12 (2D), J4.12 (PHI)
PIX_N: IC9.7 (QH_N), IC20.4 (2A)
RA0: IC2.8 (A0), IC8.9 (3Y)
RA1: IC2.7 (A1), IC8.7 (2Y)
RA2: IC2.6 (A2), IC8.12 (4Y)
RA3: IC2.5 (A3), IC8.4 (1Y)
RA4: IC2.4 (A4), IC7.9 (3Y)
RA5: IC2.3 (A5), IC7.7 (2Y)
RA6: IC2.2 (A6), IC7.4 (1Y)
RA7: IC2.1 (A7), IC7.12 (4Y)
RA8: IC2.23 (A8), IC6.4 (1Y)
RAM_CS_N: IC3.8 (CS_N), IC4.8 (CS_N), J4.3 (RAMCS_N), R19.2
RAM_SEL_N: IC12.8 (3Y), R19.1
RD_N: IC1.21 (RD_N), IC17.1 (1A), J4.31 (RD_N)
RESET_N: IC1.26 (RESET_N), J4.41 (RESET_N), R21.2, RST1.1 (RST_N)
RFSH_N: IC1.28 (RFSH_N), IC6.1 (S), IC7.1 (S), IC8.1 (S), IC16.1 (1A), J4.45 (RFSH_N)
ROM_CS1: IC2.20 (CS1), IC6.7 (2Y)
ROM_SEL_N: IC6.6 (2B), IC12.11 (4Y)
SHIFT_CLK: C9.2, IC9.2 (CLK), R2.1
SYNC: IC18.1 (1CLR_N), IC19.5 (1Q), IC21.1 (CKB), J2.2 (SYNC_N)
SYNC_ARM_N: IC18.6 (1Q_N), IC19.12 (2D)
SYNC_NEXT: IC19.2 (1D), IC19.9 (2Q)
VCC: IC1.11 (VCC), IC2.24 (VCC), IC3.18 (VCC), IC4.18 (VCC), IC5.20 (VCC), IC6.16 (VCC), IC7.16 (VCC), IC8.16 (VCC), IC9.16 (VCC), IC10.16 (VCC), IC11.14 (VCC), IC12.14 (VCC), IC13.14 (VCC), IC14.14 (VCC), IC15.14 (VCC), IC16.14 (VCC), IC17.14 (VCC), IC18.3 (1CLK), IC18.10 (2PRE_N), IC18.13 (2CLR_N), IC18.14 (VCC), IC19.4 (1PRE_N), IC19.10 (2PRE_N), IC19.13 (2CLR_N), IC19.14 (VCC), IC20.14 (VCC), IC21.5 (VCC), J1.1 (VCC), J4.2 (VCC5), R3.1, R12.1, R13.2, R14.2, R15.2, R16.2, R17.2, R18.1, R20.1, R21.1, R22.1, R23.1, R28.1, RST1.8 (VCC), X1.14 (VCC)
VIDEO: IC20.6 (2Y), J2.1 (VIDEO)
VS_N: IC11.8 (3Y), IC11.12 (4A), IC19.1 (1CLR_N)
VS_RESET: IC11.10 (3B), IC11.11 (4Y), IC21.2 (R01), IC21.3 (R02)
WAIT_N: IC1.24 (WAIT_N), J4.37 (WAIT_N), R23.2
WR_N: IC1.22 (WR_N), IC3.10 (WE_N), IC4.10 (WE_N), IC17.4 (2A), J4.33 (WR_N)
